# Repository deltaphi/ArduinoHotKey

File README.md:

# ArduinoHotKey - An Arduino-Based USB Hotkey-Keyboard

This project started because I needed a dedicated button to mute/unmute myself in Voicecalls.
Mute/Unmute functionality is avilable as a Hotkey-Combination, but why pressm ore buttons than necessary?
This project will let you use an Arduino with an Atmega32u4 Processor (e.g., Arduino Pro Micro) to sond arbitrary Key sequences to a USB host device (such as your PC or Mac).
It can send all key sequences that the Arduino Keyboard Library can produce.

## Software

A simple Arduino sketch that can read a number of digital inputs and procude arbitrary key sequences on button press.
Customize the Code to configure the key sequence of your needs.

## Hardware

A simple PCB based around a bunch of Cherry MX PCB-mount switches and an Arduino Pro Micro. Includes Hardware-Deboundinc to be extra-fancy.

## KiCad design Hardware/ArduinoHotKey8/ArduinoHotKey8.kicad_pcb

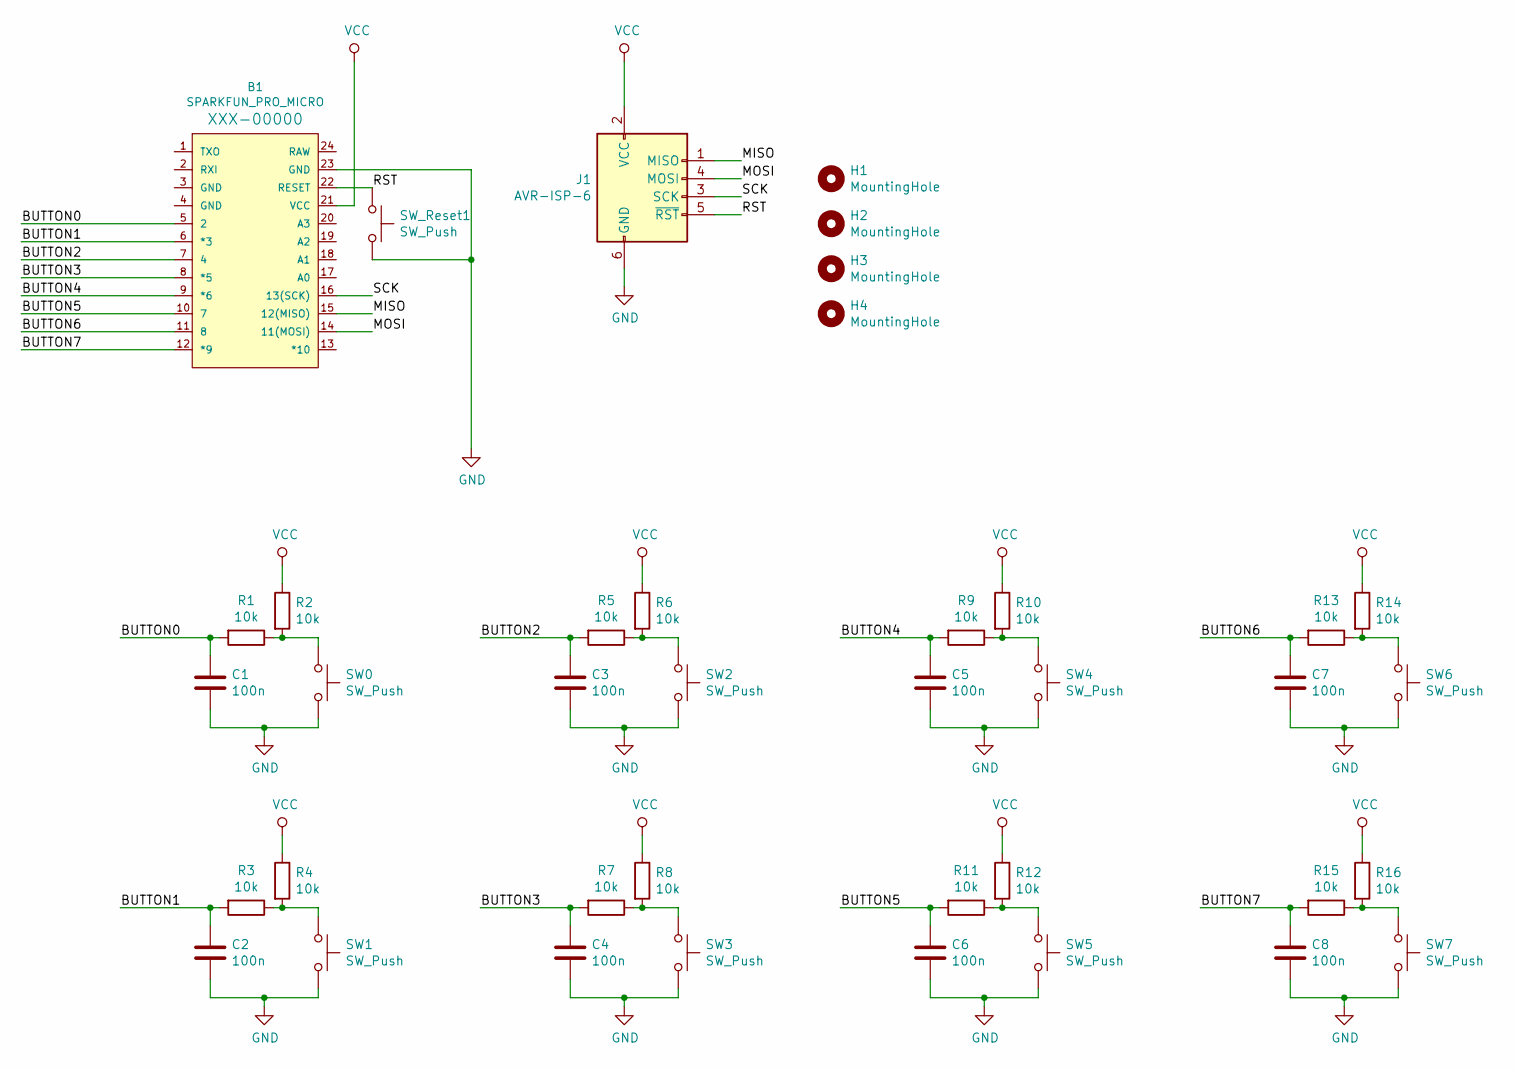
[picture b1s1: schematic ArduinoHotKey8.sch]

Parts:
B1: SPARKFUN_PRO_MICRO
C1, C2, C3, C4, C5, C6, C7, C8: 100n; C_Disc_D3.0mm_W1.6mm_P2.50mm
H1, H2, H3, H4: MountingHole; MountingHole_3.2mm_M3
J1: AVR-ISP-6; IDC-Header_2x03_P2.54mm_Vertical
R1, R2, R3, R4, R5, R6, R7, R8, R9, R10, R11, R12, R13, R14, R15, R16: 10k; R_Axial_DIN0207_L6.3mm_D2.5mm_P10.16mm_Horizontal
SW0, SW1, SW2, SW3, SW4, SW5, SW6, SW7: SW_Push; SW_Cherry_MX_1.00u_PCB
SW_Reset1: SW_Push; SW_PUSH_6mm

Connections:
/BUTTON0: B1.5 (2), C1.1, R1.2
/BUTTON1: B1.6 (*3), C2.1, R3.2
/BUTTON2: B1.7 (4), C3.1, R5.2
/BUTTON3: B1.8 (*5), C4.1, R7.2
/BUTTON4: B1.9 (*6), C5.1, R9.2
/BUTTON5: B1.10 (7), C6.1, R11.2
/BUTTON6: B1.11 (8), C7.1, R13.2
/BUTTON7: B1.12 (*9), C8.1, R15.2
/MISO: B1.15 (12(MISO)), J1.1 (MISO)
/MOSI: B1.14 (11(MOSI)), J1.4 (MOSI)
/RST: B1.22 (RESET), J1.5 (~RST), SW_Reset1.1
/SCK: B1.16 (13(SCK)), J1.3 (SCK)
GND: B1.23 (GND), C1.2, C2.2, C3.2, C4.2, C5.2, C6.2, C7.2, C8.2, J1.6 (GND), SW0.2, SW1.2, SW2.2, SW3.2, SW4.2, SW5.2, SW6.2, SW7.2, SW_Reset1.2
unnamed: R1.1, R2.2, SW0.1
unnamed: R3.1, R4.2, SW1.1
unnamed: R5.1, R6.2, SW2.1
unnamed: R7.1, R8.2, SW3.1
unnamed: R9.1, R10.2, SW4.1
unnamed: R11.1, R12.2, SW5.1
unnamed: R13.1, R14.2, SW6.1
unnamed: R15.1, R16.2, SW7.1
VCC: B1.21 (VCC), J1.2 (VCC), R2.1, R4.1, R6.1, R8.1, R10.1, R12.1, R14.1, R16.1

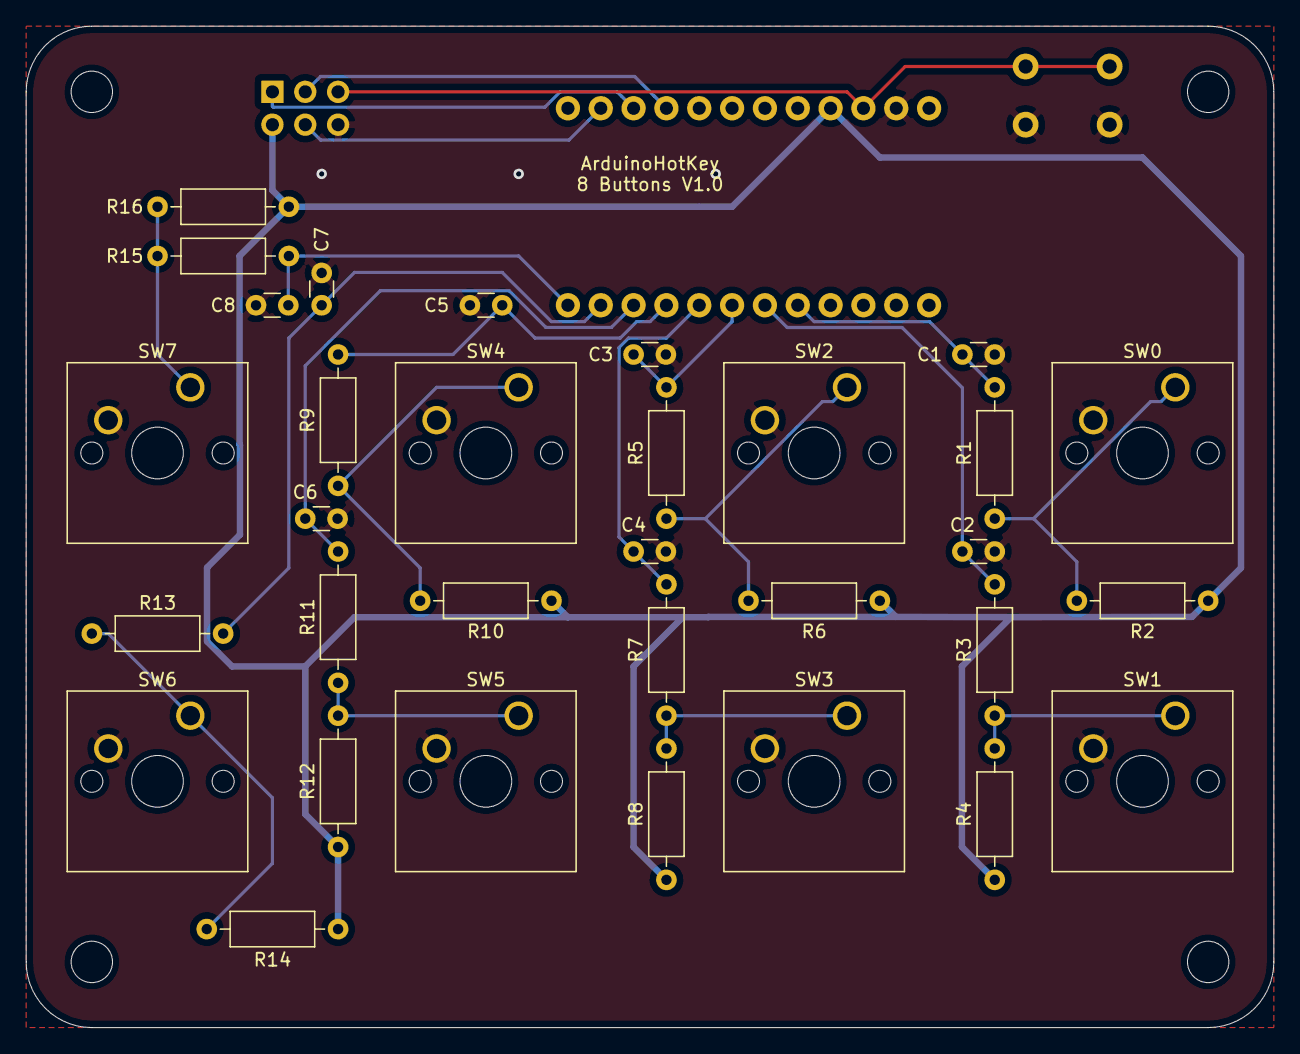
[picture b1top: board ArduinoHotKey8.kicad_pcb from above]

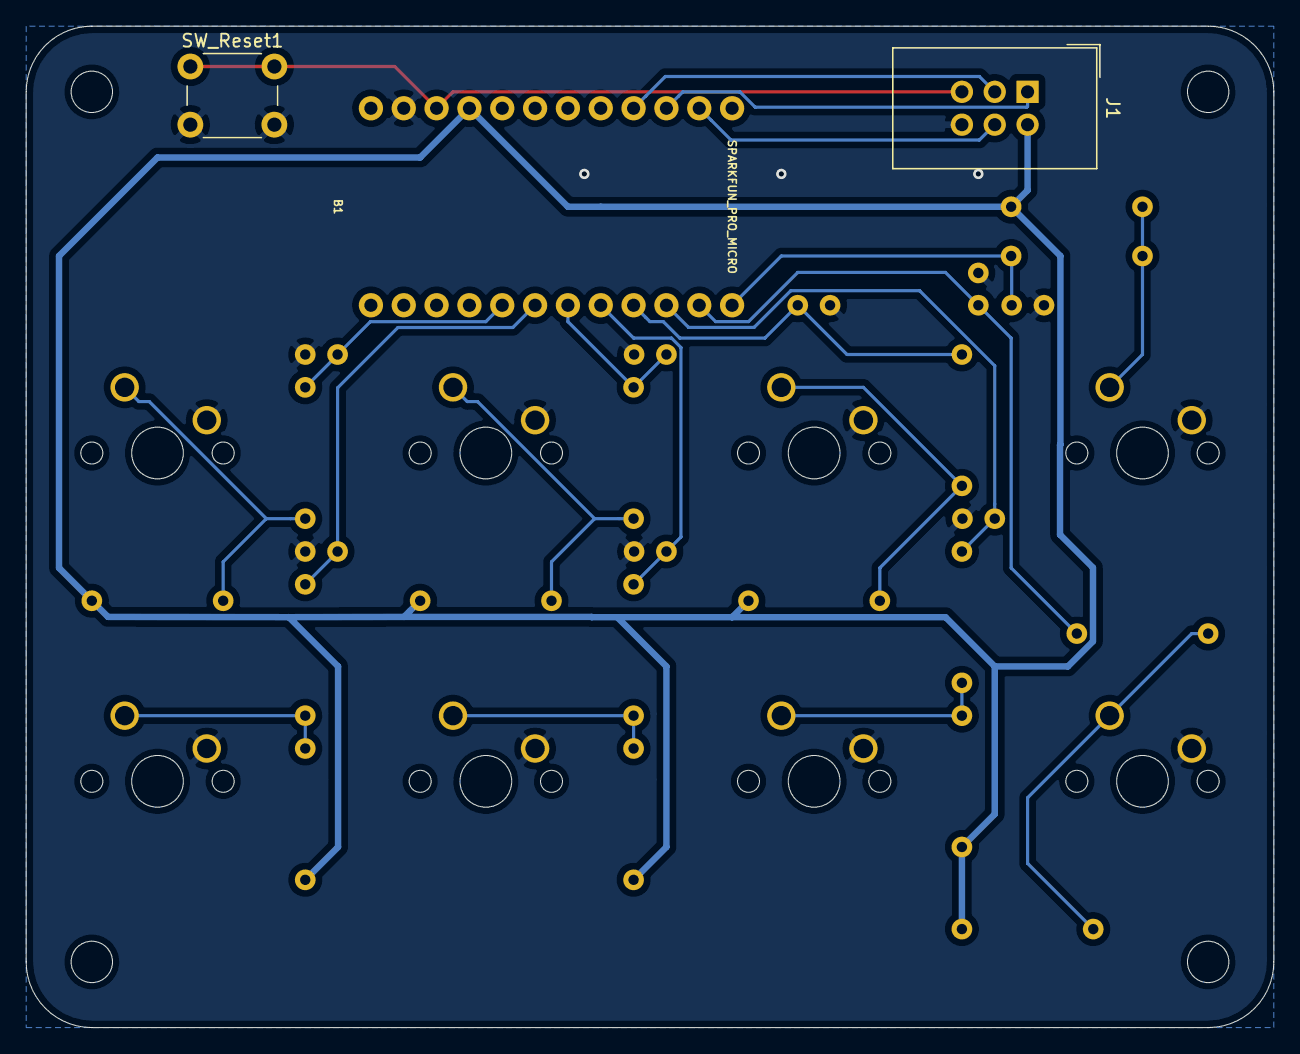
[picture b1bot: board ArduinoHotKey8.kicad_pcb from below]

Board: 2 copper layers, 96.5 x 77.5 mm, 39 parts (3 on the bottom side), 22 nets.

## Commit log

2020-04-12 Added Readme.
2020-04-12 Create ArduinoHotKey.ino
    Initial prototype Sketch for a single button.
2020-04-12 Create .gitignore
    Added .gitignore for KiCAD projects.
2020-04-12 Update ArduinoHotKey.ino
    Converted to 4-button sketch with non-identical button mapping.
    Made release delay configurable.
2020-04-12 Added empty 8-Button PCB.
2020-04-12 Added ProMini Board
    * Added Sparkfun Libraries for Arduino Pro Mini footprint.
    * Added initial project with a single Arduino board in it.
2020-04-12 Compleded Circuit
2020-04-12 First large PCB Design
2020-04-12 Update ArduinoHotKey8.kicad_pcb
    Fixed missing infill
2020-04-13 Added ISP Header
    Added ISP Header and moved bulky parts to the back
2020-04-13 Update ArduinoHotKey8.kicad_pcb
    Added Label
2020-04-13 Rearranged labels
2020-04-13 Minor improvement for USB connector
2020-04-13 Layout optimizations for USB Port
2020-04-23 Update ArduinoHotKey.ino
    Reconfigure for ArduinoHotKey8 board.
2020-04-26 Attempts at a housing with OpenSCAD
2020-04-27 Update Housing.scad
    Small fixes
2020-04-27 Update Housing.scad
    Added switch locations
2020-04-27 Improved screw-through standoffs
2020-04-27 Added front with switch holes
2020-04-27 Standoffs for the bottom done
2020-04-27 Fixed top standoff location
2020-04-27 Fixed all standoffs
2020-04-27 Added lip to bottom case
2020-04-27 Lips for bottom case
    And proper computation of lips
2020-04-27 Use computed sizes
2020-04-28 Adjust lip height to accomodate the PCB
2020-04-28 Fix length of bottom standoffs
2020-05-01 Fix first batch of errors spottet from prototype.
2020-05-05 More measurements and tolerances fixed.
2020-05-07 Added plastic for the screw head to rest on
2020-05-07 Fixed diameter of bottom screw hole
2020-05-07 Reenable topcase
2020-05-09 Fixed Standoff locations
2020-05-24 Switched to HID-Proejct library.
    Added support for Multimedia Keys.
2020-05-28 Added angled bottom case
2020-06-27 Move Sketch file.
    Sketch file places to that the repostory can directly be checked out
    into the Arduino IDE.
2020-06-27 Updates Keymappings
    Improved documentation.
    Keymappings now more useful.
2020-06-27 Bugfix Key assignments
